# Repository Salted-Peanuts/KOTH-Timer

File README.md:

# KOTH-Timer

A DIY Arduino Nano ESP32 King of the Hill timer. Built for Nerf and other objective-based skirmish games.

I originally built this timer for local Nerf events. It has since grown into a documented open-source build with physical team controls, four timer displays, battery monitoring, a local referee page and a tested PCB.

The timer runs entirely on the ESP32 and does not need an internet connection during a game.

## Current release

| | Current version |
|---|---|
| Firmware | **v0.4.0** |
| Tested PCB | **v0.2** |
| Admin page | **http://10.10.10.1/** |

Firmware:

```text
Firmware/KOTH_Timer_v0_4_0/KOTH_Timer_v0_4_0.ino
```

PCB files:

```text
PCB/v0.2-tested/
```

PCB v0.2 is still the current tested board. A revised PCB is being worked on to incorporate the v0.4 hardware changes directly.

### v0.4.0 hardware note

v0.4.0 changes the battery divider from the original 100 kΩ / 100 kΩ pair to:

```text
R1 = 10 kΩ
R2 = 10 kΩ
```

If you are upgrading an older timer or assembling PCB v0.2 for v0.4.0, use the 10 kΩ values before relying on the battery reading or low-battery protection.

The buzzer added in v0.4.0 is **optional**. The timer works normally without one.

See [v0.4.0 hardware changes](docs/hardware-upgrade-v0.4.0.md) for the upgrade details.

## How it works

Each team has its own countdown timer.

- Hold only Team A's button: Team A counts down.
- Hold only Team B's button: Team B counts down.
- Hold both buttons: the point is contested and neither team scores.
- Hold neither button: neither team scores.
- The first team to run its timer to zero wins.

The referee can start, pause, resume, reset and correct team time from the local web page.

v0.4.0 also allows a match to be started without a phone: hold both team buttons for 5 seconds while the timer is stopped.

## Referee page

The timer creates its own Wi-Fi network:

```text
SSID: KOTH-Timer
Password: none
```

After connecting, open:

```text
http://10.10.10.1/
```

Connection test:

```text
http://10.10.10.1/ping
```

The KOTH-Timer network has no internet access. If a phone or laptop warns about this, stay connected to the network.

Automatic browser opening was removed in v0.4.0 because it was inconsistent between devices. The admin address is now opened manually.

## v0.4.0 changes

The main changes from v0.3.1 are:

- 5-second physical match start using both team buttons
- optional active buzzer on D13
- scoring chirps, start countdown, victory sound and low-battery warning when a buzzer is fitted
- new winner animation on the TM1637 displays
- 10 kΩ / 10 kΩ battery divider and revised ADC calibration
- revised 5-segment battery gauge
- critical low-battery warning below 3.40 V
- automatic game freeze and saved-state recovery if the battery goes critical
- saved games restore paused after a battery swap or reboot
- cleaner referee-page control behaviour
- captive-portal code removed

Full details are in the [v0.4.0 release notes](docs/release-notes-v0.4.0.md).

## Optional buzzer

My build uses the [Keyestudio Active Buzzer Alarm Module for Arduino](https://www.keyestudio.com/products/keyestudio-active-buzzer-alarm-module-for-arduino).

Wiring:

```text
VCC -> 3.3 V
GND -> GND
SIG -> D13
```

With the buzzer fitted, the physical start sequence is:

```text
BEEP ... BEEP ... BEEEEEEP
                    ^
                    GO
```

The game starts at the beginning of the long beep.

If no buzzer is connected, all normal timer functions still work; the audible feedback is simply absent.

## Hardware

The current build uses:

- Arduino Nano ESP32
- single 18650 Li-ion cell and holder
- 5 V boost converter
- fuse and main power switch
- 2 illuminated arcade team buttons
- 4 TM1637 4-digit displays
- 5-segment battery indicator
- battery-check button
- 2 × 10 kΩ battery-divider resistors
- 220 Ω LED current-limiting resistors
- optional active buzzer
- prototype wiring or PCB v0.2
- enclosure

The current BOM is available in both formats:

- [BOM.csv](docs/BOM.csv)
- [BOM.xlsx](docs/BOM.xlsx)

## PCB revisions

| Revision | Status |
|---|---|
| **v0.1** | First manufactured board. Kept for reference; has known TM1637 display reliability issues. |
| **v0.2** | Manufactured, assembled and tested. Current recommended PCB. |
| **Next revision** | In development. Intended to incorporate the v0.4 resistor and buzzer changes directly. |

### Using PCB v0.2 with firmware v0.4.0

PCB v0.2 remains usable with v0.4.0.

Use 10 kΩ resistors at R1 and R2 instead of the original 100 kΩ values shown in the v0.2 design files.

If audible feedback is wanted, the easiest option on PCB v0.2 is to use the **DEV pinout**. It exposes D13, 3.3 V and GND, so the buzzer can be added without soldering directly to the Nano ESP32.

The original v0.2 KiCad and Gerber files have been left unchanged because they represent the board that was actually manufactured and tested.

## Build files and documentation

- [Build guide](docs/build-guide.md)
- [v0.4.0 hardware changes](docs/hardware-upgrade-v0.4.0.md)
- [v0.4.0 release notes](docs/release-notes-v0.4.0.md)
- [Documentation index](docs/README.md)
- [Changelog](CHANGELOG.md)

The firmware is written for the Arduino Nano ESP32 using Arduino IDE.

Keep the sketch inside a folder with the same base name:

```text
Firmware/
  KOTH_Timer_v0_4_0/
    KOTH_Timer_v0_4_0.ino
```

External libraries used by the firmware:

- WebSockets
- TM1637Display

Wi-Fi, WebServer and Preferences are supplied by the Arduino Nano ESP32 board package.

## Photos

### Finished prototype

### Internals

### PCB

## PCBWay

PCB v0.2 is also available as a shared PCBWay project:

[View KOTH Timer PCB v0.2 on PCBWay](https://www.pcbway.com/project/shareproject/King_Of_The_Hill_ESP32_based_timer_1aeedfa7.html)

That page shows the original v0.2 hardware. For firmware v0.4.0, use the current BOM and the v0.4 hardware notes in this repository.

PCB manufacturing for this project has been supported by [PCBWay](https://pcbway.com/g/EGJ27l).

They have been a huge help in this project. I've been very impressed by the quality of the PCBs and by the customer service. I highly recommend anyone building this for themselves to check out PCBWay's manufacturing services.  

## Licence

MIT Licence.

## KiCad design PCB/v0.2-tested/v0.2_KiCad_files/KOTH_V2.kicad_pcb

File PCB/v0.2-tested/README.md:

# KOTH Timer PCB v0.2

**Status: manufactured, assembled and tested.**

v0.2 is still the recommended PCB while the next revision is being developed.

## Using v0.2 with firmware v0.4.0

The board was designed before the v0.4 battery and buzzer changes.

For v0.4.0:

```text
R1 = 10 kΩ
R2 = 10 kΩ
```

The original design files show 100 kΩ at R1/R2. Use 10 kΩ when assembling the board for v0.4.0.

The buzzer is optional. If wanted, connect a 3.3–5 V active buzzer to:

```text
VCC -> 3.3 V
GND -> GND
SIG -> D13
```

The firmware works normally with no buzzer fitted.

## Why the KiCad files still show 100 kΩ

Those are the files for the actual v0.2 board that was manufactured and tested, so they are being kept unchanged.

The v0.4 resistor substitution is documented here, in the current BOM and in the build guide.

## Changes from v0.1

v0.2 improved:

- display power decoupling
- TM1637 CLK/DIO routing
- ground and power layout
- display reliability
- development breakout access

## Next PCB

A new revision is being worked on with the v0.4 hardware changes included on the board.

Until it has been manufactured and tested, v0.2 remains the known-good PCB.

## PCBWay

[View KOTH Timer PCB v0.2 on PCBWay](https://www.pcbway.com/project/shareproject/King_Of_The_Hill_ESP32_based_timer_1aeedfa7.html)

That page shows the original v0.2 hardware, so use the current repo BOM when building for firmware v0.4.0.

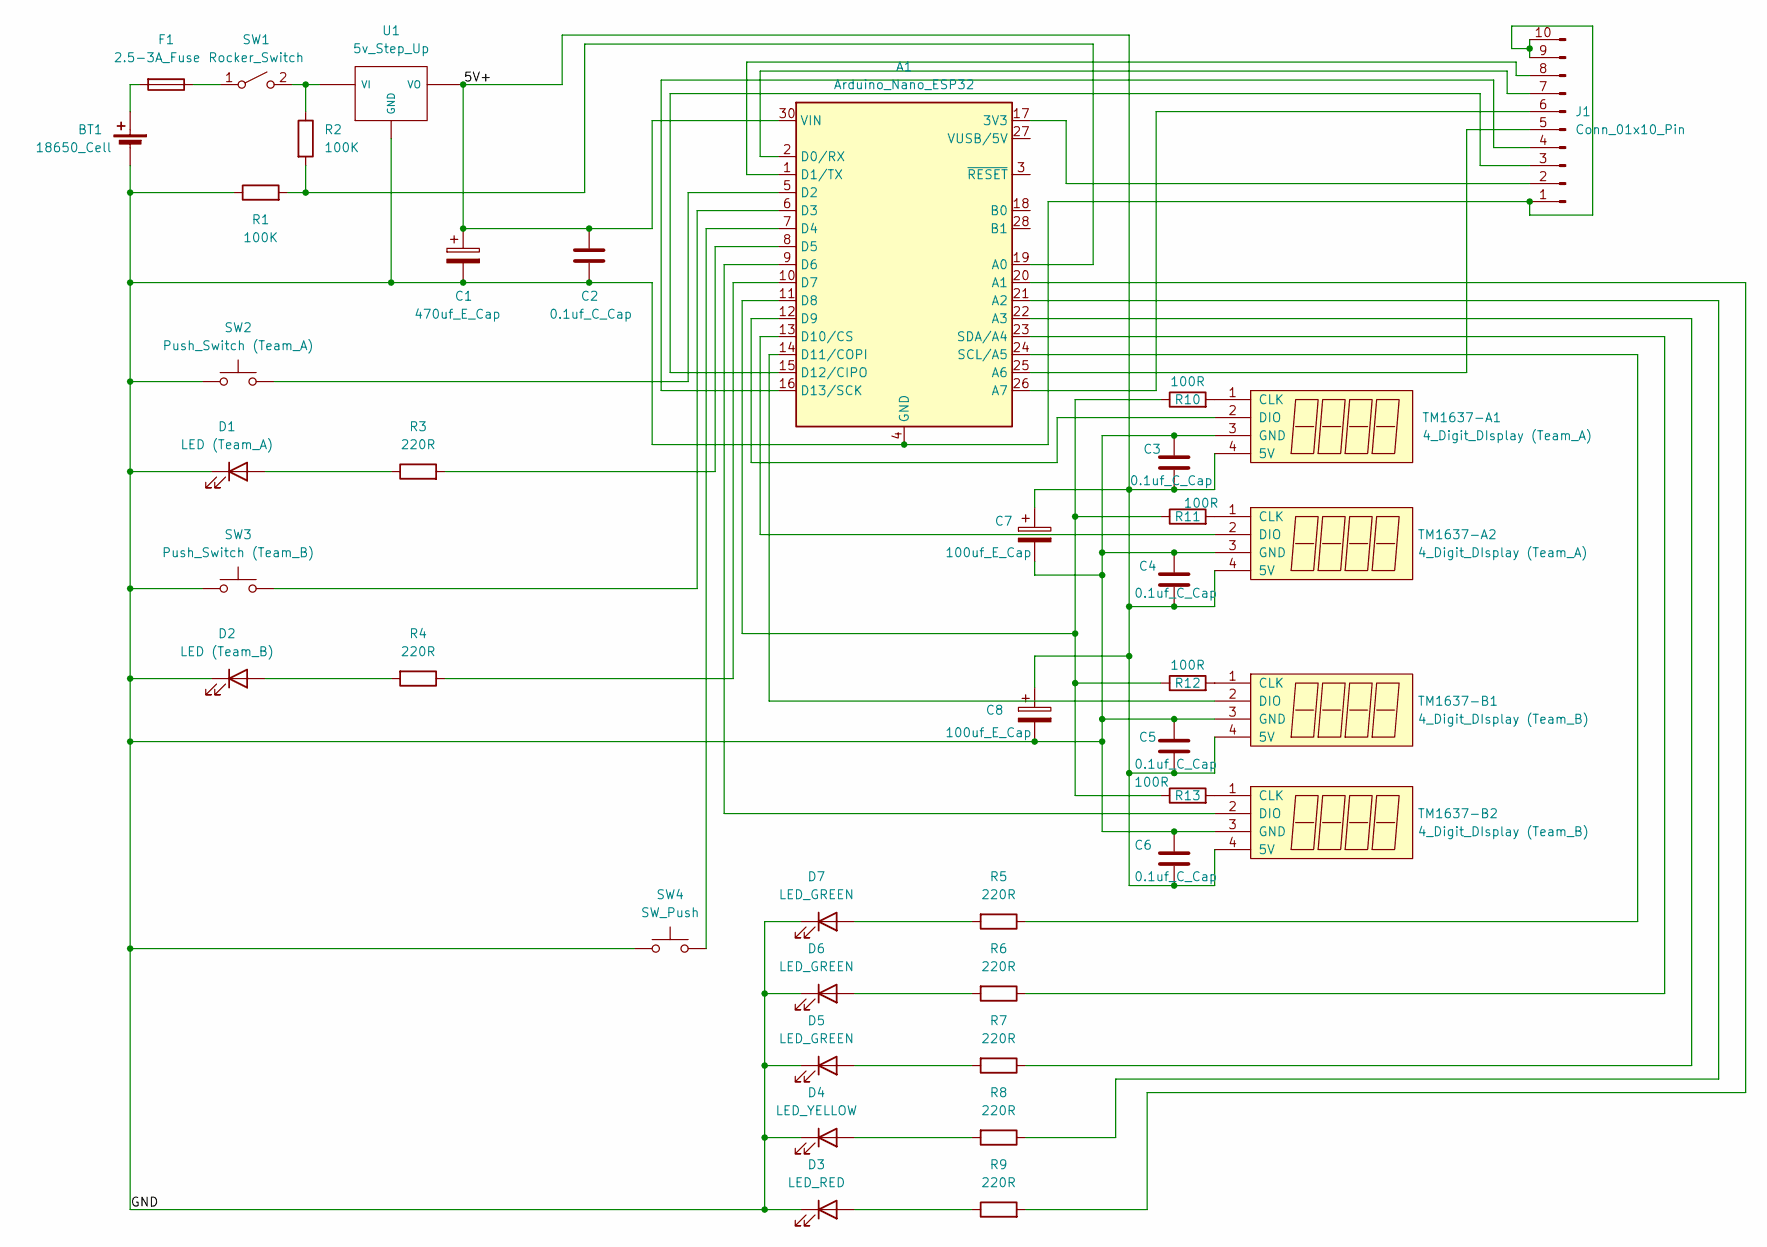
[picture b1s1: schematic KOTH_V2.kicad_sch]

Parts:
A1: Arduino_Nano_ESP32; Arduino_Nano
BT1: 18650_Cell; TerminalBlock_MaiXu_MX126-5.0-02P_1x02_P5.00mm
C1: 470uf_E_Cap; CP_Radial_D8.0mm_P5.00mm
C2, C3, C4, C5, C6: 0.1uf_C_Cap; C_Disc_D4.3mm_W1.9mm_P5.00mm
C7, C8: 100uf_E_Cap; CP_Radial_D6.3mm_P2.50mm
D1: LED (Team_A); TerminalBlock_MaiXu_MX126-5.0-02P_1x02_P5.00mm
D2: LED (Team_B); TerminalBlock_MaiXu_MX126-5.0-02P_1x02_P5.00mm
D3: LED_RED; R_Axial_DIN0207_L6.3mm_D2.5mm_P7.62mm_Horizontal
D4: LED_YELLOW; R_Axial_DIN0207_L6.3mm_D2.5mm_P7.62mm_Horizontal
D5, D6, D7: LED_GREEN; R_Axial_DIN0207_L6.3mm_D2.5mm_P7.62mm_Horizontal
F1: 2.5-3A_Fuse; Fuseholder_Clip-6.3x32mm_Littelfuse_102_122_Inline_P34.21x7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
J1: Conn_01x10_Pin; PinHeader_2x05_P2.54mm_Vertical
R1, R2: 100K; R_Axial_DIN0309_L9.0mm_D3.2mm_P15.24mm_Horizontal
R3, R4, R5, R6, R7, R8, R9: 220R; R_Axial_DIN0309_L9.0mm_D3.2mm_P15.24mm_Horizontal
R10, R11, R12, R13: 100R; R_Axial_DIN0309_L9.0mm_D3.2mm_P15.24mm_Horizontal
SW1: Rocker_Switch; TerminalBlock_MaiXu_MX126-5.0-02P_1x02_P5.00mm
SW2: Push_Switch (Team_A); TerminalBlock_MaiXu_MX126-5.0-02P_1x02_P5.00mm
SW3: Push_Switch (Team_B); TerminalBlock_MaiXu_MX126-5.0-02P_1x02_P5.00mm
SW4: SW_Push; SW_PUSH-12mm
TM1637-A1, TM1637-A2: 4_Digit_DIsplay (Team_A); TerminalBlock_MaiXu_MX126-5.0-04P_1x04_P5.00mm
TM1637-B1, TM1637-B2: 4_Digit_DIsplay (Team_B); TerminalBlock_MaiXu_MX126-5.0-04P_1x04_P5.00mm
U1: 5v_Step_Up; PinHeader_1x03_P2.54mm_Vertical

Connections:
/5V+: A1.30 (VIN), C1.1, C2.1, C3.2, C4.2, C5.2, C6.2, C7.1, C8.1, TM1637-A1.4 (5V), TM1637-A2.4 (5V), TM1637-B1.4 (5V), TM1637-B2.4 (5V), U1.3 (VO)
/GND: A1.4 (GND), A1.29 (GND), BT1.2 (-), C1.2, C2.2, C3.1, C4.1, C5.1, C6.1, C7.2, C8.2, D1.1 (K), D2.1 (K), D3.1 (K), D4.1 (K), D5.1 (K), D6.1 (K), D7.1 (K), J1.1, J1.9, J1.10, R1.1, SW2.1, SW3.1, SW4.1, TM1637-A1.3 (GND), TM1637-A2.3 (GND), TM1637-B1.3 (GND), TM1637-B2.3 (GND), U1.2 (GND)
unnamed: A1.17 (3V3), J1.2
unnamed: A1.19 (A0), R1.2, R2.2
unnamed: A1.20 (A1), R9.2
unnamed: A1.21 (A2), R8.1
unnamed: A1.22 (A3), R7.1
unnamed: A1.25 (A6), J1.5
unnamed: A1.26 (A7), J1.6
unnamed: A1.2 (D0/RX), J1.7
unnamed: A1.1 (D1/TX), J1.8
unnamed: A1.5 (D2), SW2.2
unnamed: A1.6 (D3), SW3.2
unnamed: A1.7 (D4), SW4.2
unnamed: A1.8 (D5), R3.2
unnamed: A1.9 (D6), TM1637-B2.2 (DIO)
unnamed: A1.10 (D7), R4.1
unnamed: A1.11 (D8), R10.1, R11.1, R12.1, R13.1
unnamed: A1.12 (D9), TM1637-A1.2 (DIO)
unnamed: A1.13 (D10/CS), TM1637-A2.2 (DIO)
unnamed: A1.14 (D11/COPI), TM1637-B1.2 (DIO)
unnamed: A1.15 (D12/CIPO), J1.3
unnamed: A1.16 (D13/SCK), J1.4
unnamed: A1.24 (SCL/A5), R5.1
unnamed: A1.23 (SDA/A4), R6.1
unnamed: BT1.1 (+), F1.2
unnamed: D1.2 (A), R3.1
unnamed: D2.2 (A), R4.2
unnamed: D3.2 (A), R9.1
unnamed: D4.2 (A), R8.2
unnamed: D5.2 (A), R7.2
unnamed: D6.2 (A), R6.2
unnamed: D7.2 (A), R5.2
unnamed: F1.1, SW1.1 (A)
unnamed: R2.1, SW1.2 (B), U1.1 (VI)
unnamed: R10.2, TM1637-A1.1 (CLK)
unnamed: R11.2, TM1637-A2.1 (CLK)
unnamed: R12.2, TM1637-B1.1 (CLK)
unnamed: R13.2, TM1637-B2.1 (CLK)

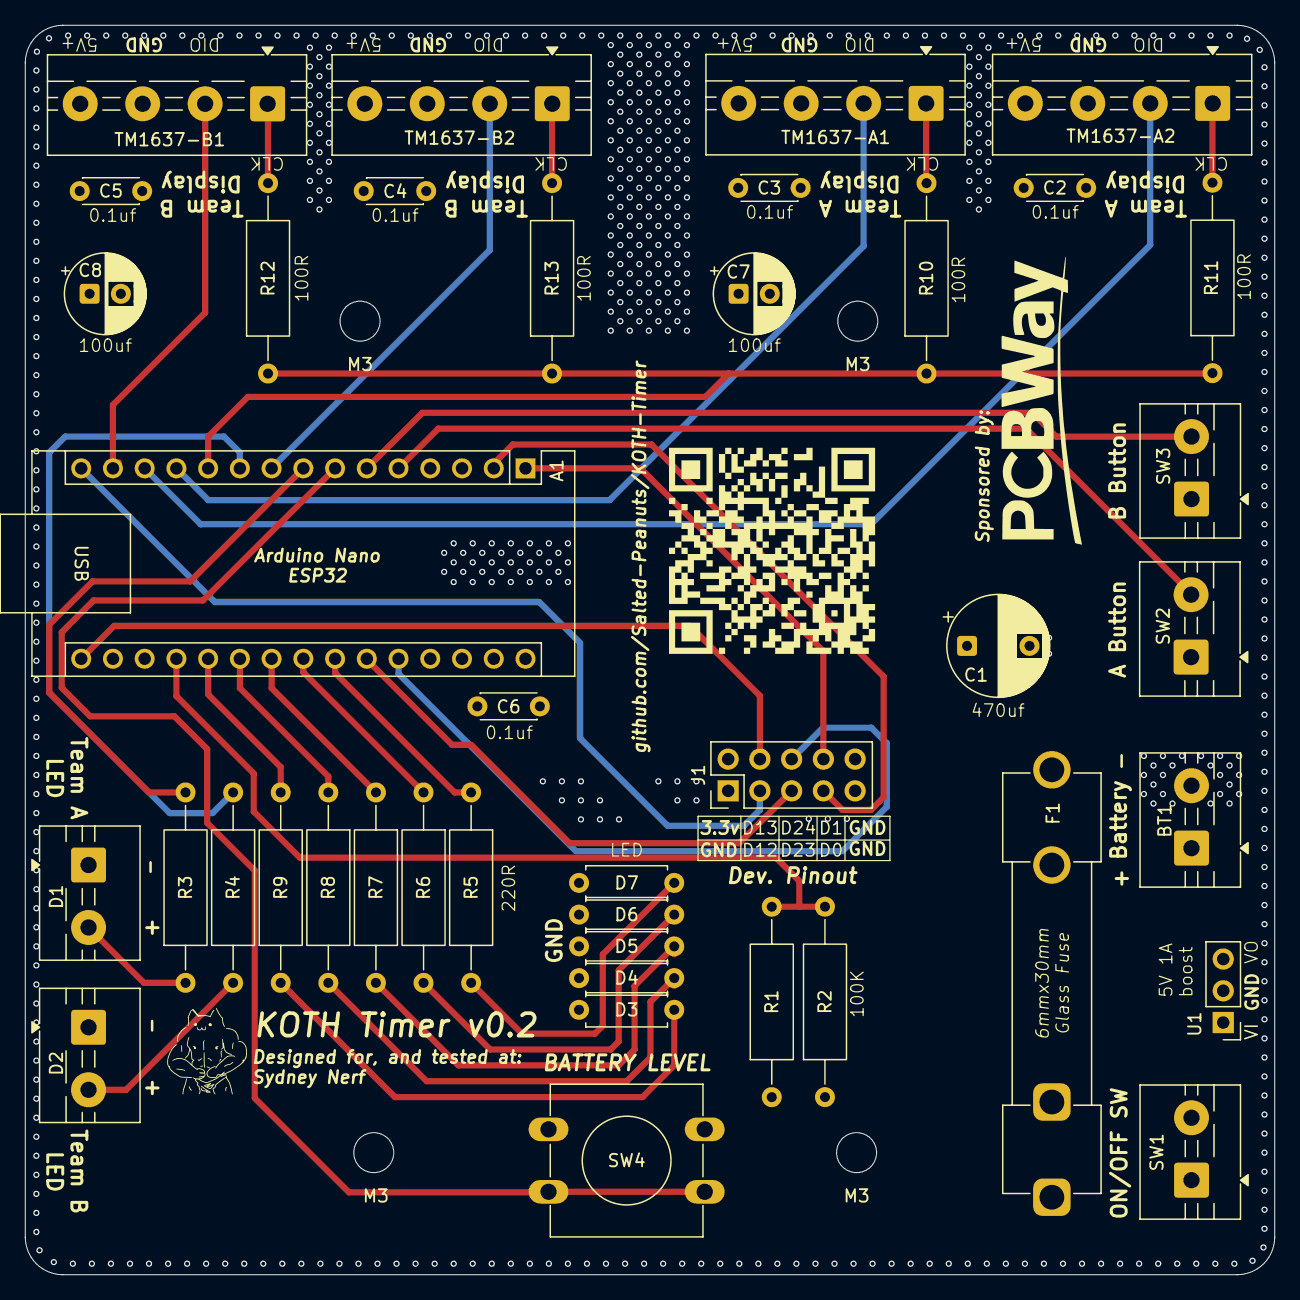
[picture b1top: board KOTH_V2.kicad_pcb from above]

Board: 4 copper layers, 100.0 x 100.0 mm, 47 parts (1 on the bottom side), 39 nets.

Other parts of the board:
M3, M3#2, M3#3, M3#4: MountingHole_3.2mm_M3
QR*****: QRKOTH-Timer
QR*****#2: QRKOTH-Timer

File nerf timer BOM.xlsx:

Reference | Qty | Value | Description: | Product links:
A1 | 1x | Arduino_Nano_ESP32 | Arduino branded ESP32 Board (Code will not work with generic ESP32 family devic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 | https://core-electronics.com.au/arduino-nano-esp32.html
BT1 | 1x | 18650_Cell | 18650 battery cell | https://www.jaycar.com.au/18650-samsung-3500mah-3-7v-flat-to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
C1 | 1x | 470uf_E_Cap | 470uf electrolytic capacitor | https://www.jaycar.com.au/470uf-16vdc-low-esr-electrolytic-c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
C2 | 1x | 0.1uf_C_Cap | 0.1uf (100nf) ceramic capacitor | https://www.jaycar.com.au/100nf-50vdc-ceramic-capacitors-pac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
D3,D4,D5,D6,D7 | 1x | LED_RED, LED_YELLOW, LED_GREEN | 5 segement LED bar graph (any colours you prefer. I used one with 3x green bars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 | https://www.aliexpress.com/item/1005010479786364.html
F1 | 1x | 2.5-3A_Fuse | 2.5a-3a Glass tube fuse with some sort of holder (Use wire thicker than your fu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 | https://www.aliexpress.com/item/1005007846817140.html
R1,R2 | 2x | 100K | 100k resistor | https://www.jaycar.com.au/100k-ohm-0-5-watt-metal-film-resis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
R3,R4,R5,R6,R7,R8,R9 | 7x | 220R | 220R resistor | https://www.jaycar.com.au/220k-ohm-0-5-watt-metal-film-resis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
SW1 | 1x | Rocker_Switch | on/off rocker style (or your prefence) for device power on and off | https://www.aliexpress.com/item/4001108045600.html
SW2,SW3,D1,D2 | 2x | Push_Switch (Team_A), Push_Switch (Team_B) | 100mm Arcade style push buttons with LEDs | https://www.aliexpress.com/item/33029152680.html
SW4 | 1x | SW_Push | PCB button switch: For turning 5 segment display on to see battery level | https://www.jaycar.com.au/spst-pcb-mount-tactile-switch-roun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
TM1637 | 4x | 4_Digit_DIsplay (Team_A), 4_Digit_DIsplay (Team_B) | TM1637 4-digit 7-segment display (2x of two diffent colours for each teams time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 | https://www.aliexpress.com/item/1005001582129952.html
U1 | 1x | 5v_Step_Up | 0.9-5V to 5V DC-DC Step-Up Power Module | https://www.amazon.com.au/dp/B0CWXM62Y5?ref=ppx_yo2ov_dt_b_f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
 | 1x | 18650 battery cell holder | you can also find them local at jaycar | https://www.amazon.com.au/dp/B0CQ73GFVY?ref=ppx_yo2ov_dt_b_f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
 |  | PCBs | Prototyping PCBs (for soldering eveything to) | https://www.aliexpress.com/item/1005007549507093.html
 |  | Insulated wire (I used 22 AWG) | Insulated wire (I used 22 AWG)
 |  | Heat shrink
 |  | Arduino Nano Breakout board
 |  | Terminal blocks as required

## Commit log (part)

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2026-05-25 Rename KOTH_timer.ino to KOTH_timer_v0.2.ino
2026-05-25 Rename KOTH_timer_v0.2.ino to v0.2_KOTH_timer.ino
2026-05-25 Rename nerf timer.pdf to KOTH_schematic.pdf
2026-05-25 Rename KOTH_schematic.pdf to Wiring_schematic.pdf
2026-05-25 Rename nerf timer BOM.xlsx to BOM.xlsx
2026-06-07 Update README.md
    Road map Updated
2026-06-19 Update and rename Firmware/v0.2_KOTH_timer.ino to Firmware/KOTH_Timer_v0_3/KOTH_Timer_v0_3.ino
    Add v0.3 pre-release firmware
2026-06-19 Update build-guide.md
    v0.3-Dev updated build guide
2026-06-24 Update README.md
    Update documentation for stable v0.3 release
